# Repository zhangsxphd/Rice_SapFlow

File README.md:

# Rice_SapFlow - 水稻茎流测量系统 (Sap Flow Meter)

[-brightgreen.svg)]()

基于热比法（Heat Ratio Method, HRM）与高精度温度传感器的水稻茎流微脉冲测量系统。包含**主控板 (Main Controller)** 与 **柔性探针板 (Sensor FPC)**，配套基于 ESP32-C3 的双 TMP117 采集与受控热脉冲固件。

---

## 目录
- [系统架构](#系统架构)
- [硬件特性与设计规范](#硬件特性与设计规范)
- [原理图与 PCB 设计](#原理图与-pcb-设计)
- [仓库目录结构](#仓库目录结构)
- [固件与使用说明](#固件与使用说明)
- [制造与打样规范 (JLCPCB)](#制造与打样规范-jlcpcb)
- [验证与交付状态](#验证与交付状态)

---

## 系统架构

```mermaid
flowchart LR
    subgraph MC["Main_Controller_V01 (主控板)"]
        ESP["ESP32-C3 SuperMini<br/>(2×8 2.54mm 排母插拔式)"]
        PWR["电源滤波与稳压<br/>5V / 3.3V / 3.0V 受控源"]
        I2C["I²C 总线<br/>4.7kΩ 上拉"]
        MOS["AO3400A N-MOS<br/>低边加热控制<br/>100Ω 栅极 + 100kΩ 下拉"]
        J1["6P 0.5mm 翻盖 FPC 连接器"]
    end

    subgraph FPC["Sensor_FPC_V01 (柔性探针)"]
        J4["6P 0.5mm 连接座 / 金手指"]
        U2["TMP117_UP (上游测温)<br/>I²C: 0x48 (ADD0=GND)<br/>100nF 去耦"]
        R5["PTC/精密加热电阻 (470Ω)<br/>中心距: 3.0 mm"]
        U3["TMP117_DOWN (下游测温)<br/>I²C: 0x49 (ADD0=3.3V)<br/>100nF 去耦"]
    end

    J1 <==>|6P 0.5mm FFC 柔性排线| J4
    ESP -->|I²C 总线| I2C --> J1
    ESP -->|HEATER_EN| MOS --> J1
```

---

## 硬件特性与设计规范

### 1. Main_Controller_V01 (主控板)
* **主控模块**：ESP32-C3 SuperMini 插拔模块（2×8 Pin、2.54 mm 间距排针/排母，17.78 mm 跨距）。
* **电源方案**：USB 5V 输入，模块板载稳压输出 3.3V，配有独立受控 3.0V 加热回路及电源去耦网络（10 µF + 100 nF）。
* **低边开关**：AO3400A N-MOSFET，用于加热低边控制；Gate 经 100 Ω 驱动电阻连接 GPIO，100 kΩ 下拉到 GND，确保启动及复位时可靠关断。
* **接口线序 (6P 0.5mm FPC)**：
  1. `+3V3`：传感器供电
  2. `GND`：参考地
  3. `SDA`：I²C 数据
  4. `SCL`：I²C 时钟
  5. `HEATER_VCC`：加热正极
  6. `HEATER_RETURN`：MOSFET 切换的加热回流

### 2. Sensor_FPC_V01 (柔性探针)
* **测温传感器**：2 颗高精度数字温度计 TMP117MAIDRVR (WSON-6, ±0.1°C 精度, 0.0078125°C 分辨率)。
  * 上游传感器 `U2`：ADD0 接地，I²C 地址 `0x48`。
  * 下游传感器 `U3`：ADD0 接 3.3V，I²C 地址 `0x49`。
  * 独立去耦：每颗 TMP117 紧邻配置 100 nF (0402) 陶瓷电容。
* **热隔离设计**：
  * **严格零铜箔隔离区**：传感器与加热源区域**绝对禁止铺铜**，避免横向热窜扰影响植物生理测量。
  * **纯正交对称走线 (Manhattan Routing)**：信号与电源线分置东西双侧走线廊道，中心仅留测温探头。
  * **过孔外移 (Off-Pad Dogbone)**：过孔均放置在焊盘外侧，杜绝回流焊吸锡漏锡风险。

---

## 原理图与 PCB 设计

### 主控板 (Main Controller)
| 原理图 | PCB 布局 |
| :---: | :---: |
|  |  |

### 柔性探针 (Sensor FPC)
| 原理图 | PCB 布局 |
| :---: | :---: |
|  |  |

---

## 仓库目录结构

```text
├── Rice_SapFlow_Optimized.epro2      # 嘉立创 EDA 专业版原生工程交付文件
├── Rice_SapFlow_Optimized_BOM.csv    # 优化版本物料清单 (BOM)
├── Rice_SapFlow_Complete_BOM.csv     # 完整器件选型清单 (含 LCSC 编号)
├── Rice_SapFlow_Complete_Netlist.enet# 嘉立创标准工程完整网络表
├── HANDOVER_TO_CODEX.md              # 工程交接说明与实物验证关键点
├── README.md                         # 项目总览文档 (本文件)
├── docs/                             # 设计文档、优化报告与矢量图表
│   ├── OPTIMIZED_DESIGN.md           # 电路、针脚、操作方法与实物验收步骤
│   ├── Rice_SapFlow_Final_Delivery_Report.md # 终期交付验证报告
│   └── *.svg                         # 高清矢量原理图与布局图
├── firmware/                         # ESP32-C3 采集与热脉冲固件
│   ├── RiceSapFlow/                  # Arduino/ESP-IDF 固件源码
│   │   ├── RiceSapFlow.ino           # 主程序 (WiFi AP, Web UI, CSV, 定时保护)
│   │   └── RiceSapFlow.ino.merged.bin# 可直接烧录的固件镜像
│   └── test_measurement.cpp         # 测量与解析算法主机测试用例
├── fabrication/                      # 嘉立创制造与工艺打样指南
│   └── JLCPCB_Fabrication_Guide.md
├── scripts/                          # 自动化建库、布线与验证脚本
├── design/                           # 参数化设计规范及需求配置
└── verification/                     # 原生 DRC、网表对账与操作审计日志
```

---

## 固件与使用说明

固件源码位于 `firmware/RiceSapFlow/`，使用 Arduino ESP32 Core (v3.3.12) 构建，编译目标 FQBN 为 `esp32:esp32:esp32c3:CDCOnBoot=cdc`。

### 编译与烧录
```bash
# 编译固件
arduino-cli compile --fqbn esp32:esp32:esp32c3:CDCOnBoot=cdc firmware/RiceSapFlow

# 烧录固件
arduino-cli upload -p /dev/tty.usbmodem* --fqbn esp32:esp32:esp32c3:CDCOnBoot=cdc firmware/RiceSapFlow
```

### 操作流程
1. 上电后，串口 (115200 波特率) 输出随机 WiFi 热点 SSID `RiceSapFlow-xxxx` 及动态密码。
2. 手机或电脑连接该热点，在浏览器中访问 `http://192.168.4.1`，输入用户名 `admin` 及热点密码。
3. 网页仪表盘提供：
   - 实时双通道温度与差值曲线（1 Hz 刷新，内部 10 Hz 采样）
   - 单次脉冲触发控制（默认 200 ms，带基线稳定前置检测与硬件定时器超时强制关断保护）
   - 历史温升数据 CSV 下载与状态监控。

---

## 制造与打样规范 (JLCPCB)

1. **主控板 (Main_Controller_V01)**：
   - 结构：双层 FR-4 板，厚度 1.6 mm，1 oz 铜厚。
   - 工艺：无铅喷锡 (Lead-free HASL) 或沉金 (ENIG)，阻焊颜色任意（推荐蓝/绿）。
2. **传感器板 (Sensor_FPC_V01)**：
   - 结构：双面聚酰亚胺 (PI) FPC 软板，基材厚度 0.1 mm，0.5 oz 铜厚。
   - 工艺：**必须选择沉金 (ENIG)**。
   - 补强要求：金手指/接插端背面需贴合 **0.2 mm 聚酰亚胺 (PI) 或 FR-4 补强片 (Stiffener)**，以满足 0.5 mm 间距翻盖式 FPC 插座的 0.3 mm 插合厚度。
   - 贴片提示：TMP117 底部裸露热焊盘（Exposed Pad）首版建议钢网开孔率设为 0%（不涂锡膏），由引脚固定焊接，防止焊锡形成热导旁路。

---

## 验证与交付状态

- **原理图 ERC**：`passed: true, total: 0`（0 悬空引脚、0 悬空网络、0 冲突）。
- **PCB 原生 DRC**：两块板在嘉立创 EDA 专业版中经原生引擎检查，结果均为 `passed: true, violations: []`（**0 错误、0 警告**）。
- **制造规范 (DFM)**：无悬空线、无尖角走线、无间距冲突、丝印均已完成自动避让无压焊盘。

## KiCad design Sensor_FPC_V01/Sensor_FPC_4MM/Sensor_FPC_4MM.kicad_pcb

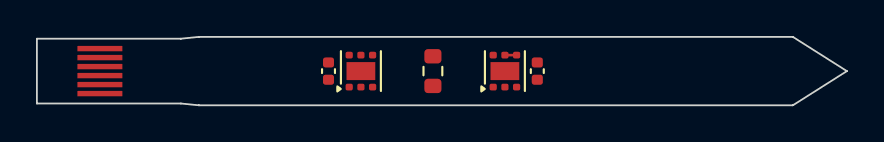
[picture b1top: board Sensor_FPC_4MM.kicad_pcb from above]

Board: 2 copper layers, 45.0 x 3.8 mm, 6 parts (0 on the bottom side), 6 nets.

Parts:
C1, C2: 100nF; C_0402_1005Metric
J1_FPC: GoldFinger_6P
R_HEAT: PTC_470R; R_0603_1608Metric
U1: TMP117_UP; WSON-6-1EP_2x2mm_P0.65mm_EP1x1.6mm
U2: TMP117_DN; WSON-6-1EP_2x2mm_P0.65mm_EP1x1.6mm

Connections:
+3V3: C1.1, C2.1, J1_FPC.1, U1.5, U2.4, U2.5
GND: C1.2, C2.2, J1_FPC.2, U1.2, U1.4, U2.2
HEATER_RETURN: J1_FPC.6, R_HEAT.2
HEATER_VCC: J1_FPC.5, R_HEAT.1
SCL: J1_FPC.4, U1.1, U2.1
SDA: J1_FPC.3, U1.6, U2.6

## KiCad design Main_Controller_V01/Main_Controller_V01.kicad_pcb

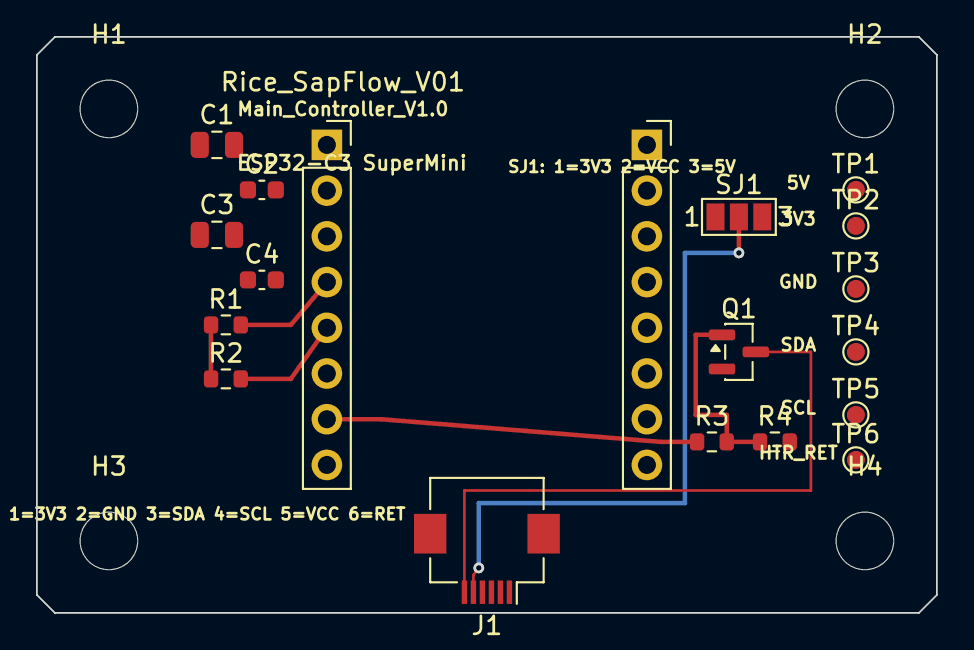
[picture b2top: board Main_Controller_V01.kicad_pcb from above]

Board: 2 copper layers, 50.0 x 32.0 mm, 23 parts (0 on the bottom side), 9 nets.

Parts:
C1, C3: 10uF; C_0805_2012Metric
C2, C4: 100nF; C_0603_1608Metric
H1, H2, H3, H4: M3; MountingHole_3.2mm_M3
J1: FPC-0.5-6P; Hirose_FH12-6S-0.5SH_1x06-1MP_P0.50mm_Horizontal
Q1: AO3400A; SOT-23
R1, R2: 4.7k; R_0603_1608Metric
R3: 100R; R_0603_1608Metric
R4: 100k; R_0603_1608Metric
SJ1: 3V3/5V; SolderJumper-3_P1.3mm_Open_Pad1.0x1.5mm_NumberLabels
TP1: 5V; TestPoint_Pad_D1.0mm
TP2: 3V3; TestPoint_Pad_D1.0mm
TP3: GND; TestPoint_Pad_D1.0mm
TP4: SDA; TestPoint_Pad_D1.0mm
TP5: SCL; TestPoint_Pad_D1.0mm
TP6: HTR_RET; TestPoint_Pad_D1.0mm
U1_L: SuperMini_L; PinSocket_1x08_P2.54mm_Vertical
U1_R: SuperMini_R; PinSocket_1x08_P2.54mm_Vertical

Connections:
+3V3: C3.1, C4.1, J1.1, R1.1, R2.1, SJ1.1, TP2.1, U1_L.3
+5V: C1.1, C2.1, SJ1.3, TP1.1, U1_L.1
GND: C1.2, C2.2, C3.2, C4.2, J1.2, J1.MP, Q1.2, R4.2, TP3.1, U1_L.2
HEATER_EN: R3.1, U1_L.7
HEATER_GATE: Q1.1, R3.2, R4.1
HEATER_RETURN: J1.6, Q1.3, TP6.1
HEATER_VCC: J1.5, SJ1.2
SCL: J1.4, R2.2, TP5.1, U1_L.5
SDA: J1.3, R1.2, TP4.1, U1_L.4

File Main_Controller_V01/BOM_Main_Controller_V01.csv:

"Comment","Designator","Footprint","LCSC Part #"
"ESP32-C3 Super Mini Socket (1x8 2.54mm Female Header)","U1_L, U1_R","PinSocket_1x08_P2.54mm_Vertical","C42431840"
"AO3400A N-MOSFET SOT-23 30V 5.7A","Q1","SOT-23","C20917"
"4.7kΩ ±1% 0603 SMD Resistor (I2C Pull-Up)","R1, R2","R_0603_1608Metric","C23162"
"100Ω ±1% 0603 SMD Resistor (Gate Damping)","R3","R_0603_1608Metric","C22775"
"100kΩ ±1% 0603 SMD Resistor (Gate Pull-Down)","R4","R_0603_1608Metric","C25803"
"10µF 50V X5R 0805 SMD Capacitor (GRM21BR61H106KE43L)","C1, C3","C_0805_2012Metric","C440198"
"100nF 50V X7R 0603 SMD Capacitor","C2, C4","C_0603_1608Metric","C14663"
"6P 0.5mm Horizontal Flip-Lock FPC Connector","J1","Hirose_FH12-6S-0.5SH_1x06-1MP_P0.50mm_Horizontal","C202118"
"3-Pad Solder Jumper (Default OPEN; manually select one voltage)","SJ1","SolderJumper-3_P1.3mm_Open_Pad1.0x1.5mm_NumberLabels","CUSTOM_SMD"
"Test Point SMD Pad D1.0mm","TP1, TP2, TP3, TP4, TP5, TP6","TestPoint_Pad_D1.0mm","CUSTOM_TP"
"M3 Mounting Hole Dia 3.2mm","H1, H2, H3, H4","MountingHole_3.2mm_M3","MECHANICAL"

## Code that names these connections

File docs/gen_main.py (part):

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  <line x1="100" y1="440" x2="150" y2="440" stroke="#94a3b8" stroke-width="1.5"/>
  <text x="160" y="445" font-size="11" fill="#64748b">6: GPIO2 (NC)</text>

  <!-- 7: GPIO3 (HEATER_EN) -->
  <line x1="430" y1="380" x2="560" y2="380" stroke="#ea580c" stroke-width="2"/>
  <circle cx="560" cy="380" r="4" fill="#ea580c"/>
  <text x="420" y="385" text-anchor="end" font-size="11" font-weight="bold" fill="#ea580c">7: GPIO3 (HTR_EN)</text>
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  <text x="1065" y="325" font-size="12" font-weight="bold" fill="#0891b2">Pin 4: SCL</text>
  <text x="1025" y="315" font-size="10" font-weight="bold" fill="#0891b2">I2C_SCL</text>

  <!-- Pin 5: HEATER_VCC -->
  <line x1="900" y1="360" x2="1050" y2="360" stroke="#dc2626" stroke-width="2.5"/>
  <circle cx="1050" cy="360" r="4" fill="#dc2626"/>
  <text x="1065" y="365" font-size="12" font-weight="bold" fill="#dc2626">Pin 5: HEATER_VCC</text>
  <text x="990" y="355" font-size="10" font-weight="bold" fill="#dc2626">HEATER_VCC</text>

  <!-- Pin 6: HEATER_RETURN -->
  <line x1="900" y1="400" x2="1050" y2="400" stroke="#ea580c" stroke-width="2.5"/>
  <circle cx="1050" cy="400" r="4" fill="#ea580c"/>
  <text x="1065" y="405" font-size="12" font-weight="bold" fill="#ea580c">Pin 6: HEATER_RETURN</text>
  <text x="975" y="395" font-size="10" font-weight="bold" fill="#ea580c">HEATER_RETURN</text>

  <!-- Note on FPC Pitch -->
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

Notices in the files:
README.md:
License: MIT
